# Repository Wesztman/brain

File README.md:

# Brain (based on [Urchin by Duckyb](https://github.com/duckyb/urchin))

<span>

</span>

My first ever keyboard build was the Ferris Sweep, it's a wonderful keyboard! But I missed a few keys, the ctrl and shift keys on the left side and since I'm Swedish, I also wanted keys for åäö. Apart from this I was also only interested in wireless designs and was not interested in the TRRS jacks etc. The Urchin was the perfect solution for me, but I were still missing those oh so sought after keys. So I decided to make my own version of the Urchin, with a few extra keys and a little tweek to the edge cut to fit them nicely.

The result of this is the Brain, a wireless split keyboard based on the Urchin with 3 extra keys on each side. One extra pinky column with two keys and one extra thumb key. All 5 pinky keys are placed 2mm lower than the original Urchin keys, to make it easier to reach them.

**This is a strictly wireless-only design, and is only compatible with ZMK / nice!nano. Only Choc v1 switches + Hotswap are supported!**

## Features compared to [Urchin](https://github.com/duckyb/urchin)

- [x] Original pinky column lowered 2mm.
- [x] A new pinky column added with two buttons, also 2mm offset down from its neighbour.
- [x] One new thumb button added.
- [x] Holes that fit [Corne Acrylic cover](https://kriscables.com/product/corne-oled-cover-plate/) for nice!view.

## Feature requests for 2.0

- [ ] Raise last pinky column, maybe as much as 7-8 mm. For easier access to both the keys and not only the top one.
- [ ] Add back the fourth hole for tenting puck.
- [ ] Rotate the diode for switch 17, it's reversed now which causes confusion.
- [ ] Change the reset switch B3U-1000P(M) to regular tactile reset switch such as https://kriscables.com/product/tactile-reset-switch/ since it's a pain to get hold of the original reset switch.
- [ ] Do a non battery RGB blingbling version? I almost only use my keyboard without battery and a cable like this anyway https://www.amazon.se/dp/B0CYT426GZ?ref=ppx_yo2ov_dt_b_fed_asin_title&th=1

## Part list (for both sides)

#### Required

- 1× PCB Kit (files for it are in [releases](https://github.com/wesztman/brain/releases))
- 40× Kailh **CHOC** Hotswap Sockets (https://splitkb.com/products/kailh-hotswap-sockets?variant=39472161456205)
- 40× Kailh Choc v1 Switches (https://splitkb.com/collections/switches-and-keycaps/products/kailh-low-profile-choc-switches)
- 40× Keycaps 1u (https://splitkb.com/collections/switches-and-keycaps/products/blank-mbk-choc-low-profile-keycaps)
- 2× nice!nano (https://splitkb.com/products/nice-nano?_pos=1&_sid=0e4cc26b1&_ss=r)
- 40× SMD diodes (SOD-123) (https://kriscables.com/product/smd-diodes-sod123fl/)
- 48× mill-max machined pins (https://kriscables.com/product/mill-max-socket-pins/)
- 2× Pair of female mill-max headers (raised ones to fit battery) (https://kriscables.com/product/mill-max-low-profile-sockets/)
- 2× Lipo battery (301230) (https://kriscables.com/product/li-po-battery-3-7v-110mah/)
  - **OR** 1x split USB-C cable to use the keyboard without batteries (https://www.amazon.se/dp/B0CYT426GZ?ref=ppx_yo2ov_dt_b_fed_asin_title&th=1) (this also means you could go with "regular" millmax sockets and not the raised ones)
- 2x Power switch (MSK 12C02) (https://kriscables.com/product/msk-12c02-power-switch/)
  
#### Optional

- 2× nice!view (needs higher sockets to get level above raised mill-max sockets, TODO add exact ones) (https://splitkb.com/collections/keyboard-parts/products/nice-view)
- 2× Reset switch (B3U-1000P(M)) (https://www.digikey.se/sv/products/detail/omron-electronics-inc-emc-div/B3U-1000P/1534338?srsltid=AfmBOop7zspfRjYOQ7LR1wDdW5W1PJkAlY6OWJ5YXfqCBF3_GB-U63jH)
- 16× adhesive silicone feet 8mm (https://www.amazon.se/-/en/Adhesive-Silicone-Semicircle-Transparent-Furniture/dp/B09QSKVBL5)

## How do I make this?

Follow the the excellent build guide in the link below. The only difference is the 3 extra keys on each side.

Note that diodes should only be mounted on the "BOTTOM" side of the PCBs.

## Firmware

Brain supports ZMK only.

Firmware is provided by the lovely [iamDrakkir](https://github.com/iamDrakkir) and can be found in his [zmk-brain](https://github.com/iamDrakkir/zmk-brain) repo.

My personal fork can be found [here](https://github.com/Wesztman/zmk-config?organization=Wesztman&organization=Wesztman) if it's of interest for anyone (it has automatic picture generation of the layout for the readme #humbleflex)

## 3D Printed Cases

| Top | Side |
| --- | ---  |
|  |  |

| Closed | Open |
| --- | ---  |
|  |  |

## Credits

- Urchin by [duckyb](https://github.com/duckyb/urchin)
- Logo by [Ariyanto Deni](https://thenounproject.com/ariyantodeni/)
- 3D case by [iamDrakkir](https://github.com/iamDrakkir)
- ZMK Firmware [iamDrakkir](https://github.com/iamDrakkir)

## Featured In

- [KBD Issue #122](https://kbd.news/Brain-2014.html)

## License
[MIT](https://github.com/Wesztman/brain/blob/main/LICENSE)

<a href="https://star-history.com/#Wesztman/brain&Date">
 <picture>
   <source media="(prefers-color-scheme: dark)" srcset="https://api.star-history.com/svg?repos=Wesztman/brain&type=Date&theme=dark" />
   <source media="(prefers-color-scheme: light)" srcset="https://api.star-history.com/svg?repos=Wesztman/brain&type=Date" />
   
 </picture>
</a>

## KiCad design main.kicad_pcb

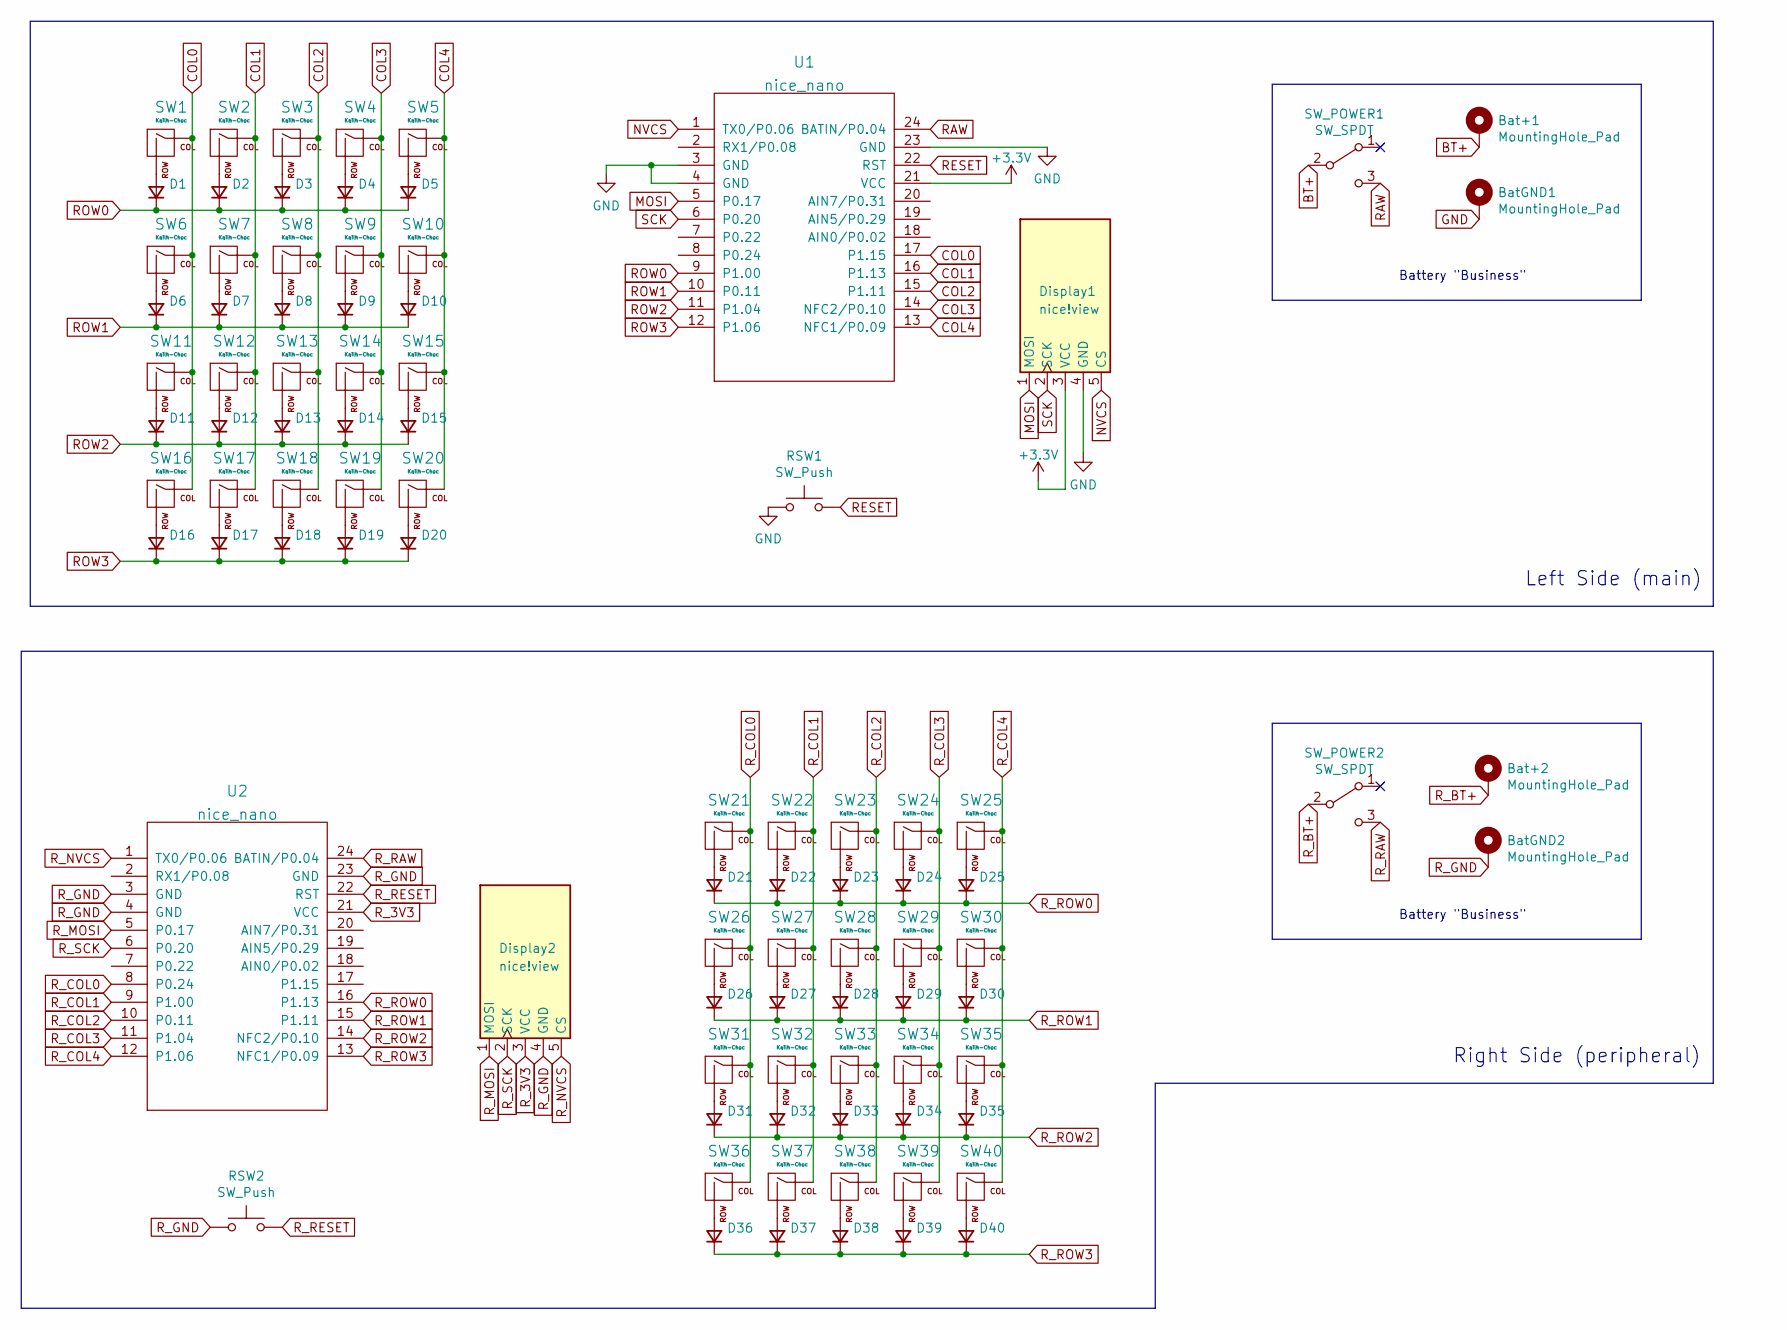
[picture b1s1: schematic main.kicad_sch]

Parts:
Bat+1, Bat+2: MountingHole_Pad; 1pin_Battery
BatGND1, BatGND2: MountingHole_Pad; 1pin_Battery
D1, D2, D3, D4, D5, D6, D7, D8, D9, D10, D11, D12, D13, D14, D15, D16, D17, D18, D19, D20, D21, D22, D23, D24, D25, D26, D27, D28, D29, D30, D31, D32, D33, D34, D35, D36, D37, D38, D39, D40: diode; SMD_Diode_Tiny
Display1, Display2: nice!view; nice_view
RSW1, RSW2: SW_Push; SW_RESET
SW1, SW2, SW3, SW4, SW5, SW6, SW7, SW8, SW9, SW10, SW11, SW12, SW13, SW14, SW15, SW16, SW17, SW18, SW19, SW20, SW21, SW22, SW23, SW24, SW25, SW26, SW27, SW28, SW29, SW30, SW31, SW32, SW33, SW34, SW35, SW36, SW37, SW38, SW39, SW40: Kailh-Choc; SW_Hotswap_Kailh_Choc_V1_tweaked
SW_POWER1, SW_POWER2: SW_SPDT; smt-slider-switch
U1, U2: nice_nano

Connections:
+3V3: Display1.3 (VCC), U1.21 (VCC)
BT+: Bat+1.1, SW_POWER1.2 (B)
COL0: SW1.1 (COL), SW6.1 (COL), SW11.1 (COL), SW16.1 (COL), U1.17 (P1.15)
COL1: SW2.1 (COL), SW7.1 (COL), SW12.1 (COL), SW17.1 (COL), U1.16 (P1.13)
COL2: SW3.1 (COL), SW8.1 (COL), SW13.1 (COL), SW18.1 (COL), U1.15 (P1.11)
COL3: SW4.1 (COL), SW9.1 (COL), SW14.1 (COL), SW19.1 (COL), U1.14 (NFC2/P0.10)
COL4: SW5.1 (COL), SW10.1 (COL), SW15.1 (COL), SW20.1 (COL), U1.13 (NFC1/P0.09)
GND: BatGND1.1, Display1.4 (GND), RSW1.1, U1.3 (GND), U1.4 (GND), U1.23 (GND)
MOSI: Display1.1 (MOSI), U1.5 (P0.17)
NVCS: Display1.5 (CS), U1.1 (TX0/P0.06)
unnamed: D1.2 (A), SW1.2 (ROW)
unnamed: D2.2 (A), SW2.2 (ROW)
unnamed: D3.2 (A), SW3.2 (ROW)
unnamed: D4.2 (A), SW4.2 (ROW)
unnamed: D5.2 (A), SW5.2 (ROW)
unnamed: D6.2 (A), SW6.2 (ROW)
unnamed: D7.2 (A), SW7.2 (ROW)
unnamed: D8.2 (A), SW8.2 (ROW)
unnamed: D9.2 (A), SW9.2 (ROW)
unnamed: D10.2 (A), SW10.2 (ROW)
unnamed: D11.2 (A), SW11.2 (ROW)
unnamed: D12.2 (A), SW12.2 (ROW)
unnamed: D13.2 (A), SW13.2 (ROW)
unnamed: D14.2 (A), SW14.2 (ROW)
unnamed: D15.2 (A), SW15.2 (ROW)
unnamed: D16.2 (A), SW16.2 (ROW)
unnamed: D17.2 (A), SW17.2 (ROW)
unnamed: D18.2 (A), SW18.2 (ROW)
unnamed: D19.2 (A), SW19.2 (ROW)
unnamed: D20.2 (A), SW20.2 (ROW)
unnamed: D21.2 (A), SW21.2 (ROW)
unnamed: D22.2 (A), SW22.2 (ROW)
unnamed: D23.2 (A), SW23.2 (ROW)
unnamed: D24.2 (A), SW24.2 (ROW)
unnamed: D25.2 (A), SW25.2 (ROW)
unnamed: D26.2 (A), SW26.2 (ROW)
unnamed: D27.2 (A), SW27.2 (ROW)
unnamed: D28.2 (A), SW28.2 (ROW)
unnamed: D29.2 (A), SW29.2 (ROW)
unnamed: D30.2 (A), SW30.2 (ROW)
unnamed: D31.2 (A), SW31.2 (ROW)
unnamed: D32.2 (A), SW32.2 (ROW)
unnamed: D33.2 (A), SW33.2 (ROW)
unnamed: D34.2 (A), SW34.2 (ROW)
unnamed: D35.2 (A), SW35.2 (ROW)
unnamed: D36.2 (A), SW36.2 (ROW)
unnamed: D37.2 (A), SW37.2 (ROW)
unnamed: D38.2 (A), SW38.2 (ROW)
unnamed: D39.2 (A), SW39.2 (ROW)
unnamed: D40.2 (A), SW40.2 (ROW)
RAW: SW_POWER1.3 (C), U1.24 (BATIN/P0.04)
RESET: RSW1.2, U1.22 (RST)
ROW0: D1.1 (K), D2.1 (K), D3.1 (K), D4.1 (K), D5.1 (K), U1.9 (P1.00)
ROW1: D6.1 (K), D7.1 (K), D8.1 (K), D9.1 (K), D10.1 (K), U1.10 (P0.11)
ROW2: D11.1 (K), D12.1 (K), D13.1 (K), D14.1 (K), D15.1 (K), U1.11 (P1.04)
ROW3: D16.1 (K), D17.1 (K), D18.1 (K), D19.1 (K), D20.1 (K), U1.12 (P1.06)
R_3V3: Display2.3 (VCC), U2.21 (VCC)
R_BT+: Bat+2.1, SW_POWER2.2 (B)
R_COL0: SW21.1 (COL), SW26.1 (COL), SW31.1 (COL), SW36.1 (COL), U2.8 (P0.24)
R_COL1: SW22.1 (COL), SW27.1 (COL), SW32.1 (COL), SW37.1 (COL), U2.9 (P1.00)
R_COL2: SW23.1 (COL), SW28.1 (COL), SW33.1 (COL), SW38.1 (COL), U2.10 (P0.11)
R_COL3: SW24.1 (COL), SW29.1 (COL), SW34.1 (COL), SW39.1 (COL), U2.11 (P1.04)
R_COL4: SW25.1 (COL), SW30.1 (COL), SW35.1 (COL), SW40.1 (COL), U2.12 (P1.06)
R_GND: BatGND2.1, Display2.4 (GND), RSW2.1, U2.3 (GND), U2.4 (GND), U2.23 (GND)
R_MOSI: Display2.1 (MOSI), U2.5 (P0.17)
R_NVCS: Display2.5 (CS), U2.1 (TX0/P0.06)
R_RAW: SW_POWER2.3 (C), U2.24 (BATIN/P0.04)
R_RESET: RSW2.2, U2.22 (RST)
R_ROW0: D21.1 (K), D22.1 (K), D23.1 (K), D24.1 (K), D25.1 (K), U2.16 (P1.13)
R_ROW1: D26.1 (K), D27.1 (K), D28.1 (K), D29.1 (K), D30.1 (K), U2.15 (P1.11)
R_ROW2: D31.1 (K), D32.1 (K), D33.1 (K), D34.1 (K), D35.1 (K), U2.14 (NFC2/P0.10)
R_ROW3: D36.1 (K), D37.1 (K), D38.1 (K), D39.1 (K), D40.1 (K), U2.13 (NFC1/P0.09)
R_SCK: Display2.2 (SCK), U2.6 (P0.20)
SCK: Display1.2 (SCK), U1.6 (P0.20)

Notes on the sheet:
Right Side (peripheral)
Battery "Business"
Left Side (main)

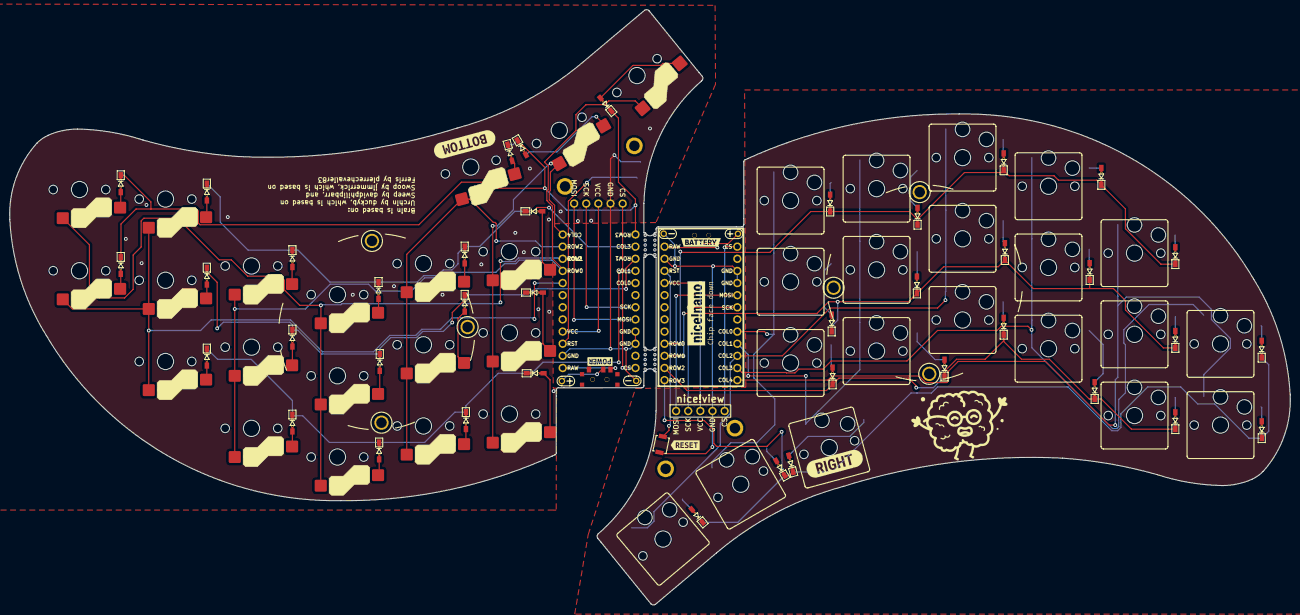
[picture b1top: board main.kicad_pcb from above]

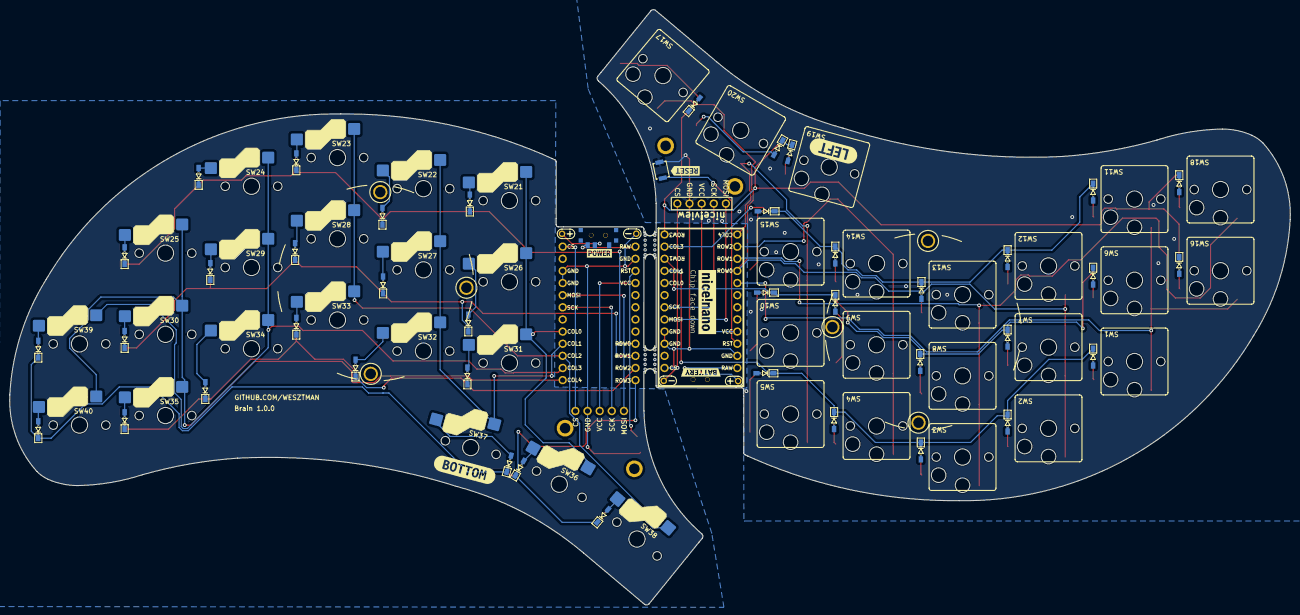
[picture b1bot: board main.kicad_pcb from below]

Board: 2 copper layers, 268.1 x 124.6 mm, 110 parts (56 on the bottom side), 74 nets.

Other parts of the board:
REF_PUCK_R: Tenting Puck; Tenting_Puck2_no_pads
REF_PUCK_R#2: Tenting Puck; Tenting_Puck2_no_pads
kibuzzard-636588C8, kibuzzard-636588C8#2: G***; kibuzzard-636588C8
kibuzzard-636592CC: G***; kibuzzard-636592CC
kibuzzard-6361375E, kibuzzard-6361375E#2: G***; kibuzzard-6361375E
kibuzzard-6365884B: G***; kibuzzard-6365884B
kibuzzard-6365950B: G***; kibuzzard-6365950B
kibuzzard-6365951E: G***; kibuzzard-6365951E
kibuzzard-63658823: G***; kibuzzard-63658823
kibuzzard-63658830: G***; kibuzzard-63658830
kibuzzard-63658865: G***; kibuzzard-63658865
kibuzzard-63659296: G***; kibuzzard-63659296
kibuzzard-63659465: G***; kibuzzard-63659465
kibuzzard-63659477: G***; kibuzzard-63659477
mouse-bite-2mm-slot, mouse-bite-2mm-slot#2: VAL**; mouse-bite-5mm-slot-with-space-for-track

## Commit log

2023-03-26 Sharp pinky corner
2023-03-26 Brain
2023-03-27 Left outline complete
2023-03-27 Components and edge cut for right pcb
2023-03-28 Update run-kibot.yml
    This change sets the kibot workflow to use kicad v7 to match your local version. This allows the automated workflow to update the PCB preview in the main readme file when you change the pcb.
2023-03-28 Updated gitignore
2023-03-28 Fixed outline for right hand
2023-03-28 Finished, time for cleanup
2023-03-28 Update gallery (automated)
2023-03-28 Flipped right board
2023-03-28 Flipped right side and added mouse bites
2023-03-28 Moved right front to right side
2023-03-28 Added brain icon
2023-03-28 Added copper icon
2023-03-28 Changed icon to copper
2023-03-30 Added pads for niceview cover
2023-03-30 Rotated back card
2023-03-30 Added missing parts to schematic.
2023-03-30 Updated schematic and updated pcb
2023-03-30 Re-annotated all labels
2023-03-31 Moved edge cut to encircle pad which was cut of before
2023-03-31 Added vias and copper fill
2023-03-31 Version 0.1.0
2023-03-31 Updated readme and license
2023-04-01 Changed icon to silkscreen
2023-04-02 remove cases for urchin
2023-04-02 Add case and preview picture
2023-04-02 Add Readme for case
2023-04-03 Fixed issue with hole cutting trace. updated version
2023-04-03 Removed alot of small unconnected traces
2023-04-03 Add rubberfeet info
2023-04-03 Fix path to pictures
2023-05-09 Update left case
2023-05-12 Updated version text to 1.0.0
2023-05-30 update case
    Add 1.5mm above the usb-output to protect the power-switch
2023-05-30 .stl files
2023-05-30 Remove .step files
2023-06-13 1mm extra at the usb cutout
2023-06-16 Moved case to new folder
2023-06-16 Added travel case
2023-06-16 Updated readmes
2024-11-01 Zmk-brain repo
2025-04-10 Add brain icons and update README with new images
